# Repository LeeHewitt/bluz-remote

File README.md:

Bluz Remote Files
==========
Bluz is a Development Kit (DK) that implements the Wiring language and talks to the [Particle](https://www.particle.io/) cloud through Bluetooth Low Energy. It can be accessed through a REST API and programmed from a Web IDE.

The Bluz Remote is a device that can be used to control many Particle projects. It provides a simple layout for buttons thaqt publish events, the events can then be subscribed to by various Particle services for control.

Example projects to control include:
* Robotic projects 
* IR Transmitters to control TV's, DVD's, etc
* RF Transmitters to control light switches, outlets, etc

Project Page: https://www.hackster.io/eely22/universe-remote-5830e2

###PCB 
The PCB is available on OSH Park:

<a href="https://oshpark.com/shared_projects/SAVrwlZ8"></img></a> 

##Sections
<b>BOM</b>: Current Bill of Materials for the remote.

<b>HW Design</b>: Schematics, board layouts, and other design files.

<b>3D Files</b>: 3D Models of the PCBA and Case

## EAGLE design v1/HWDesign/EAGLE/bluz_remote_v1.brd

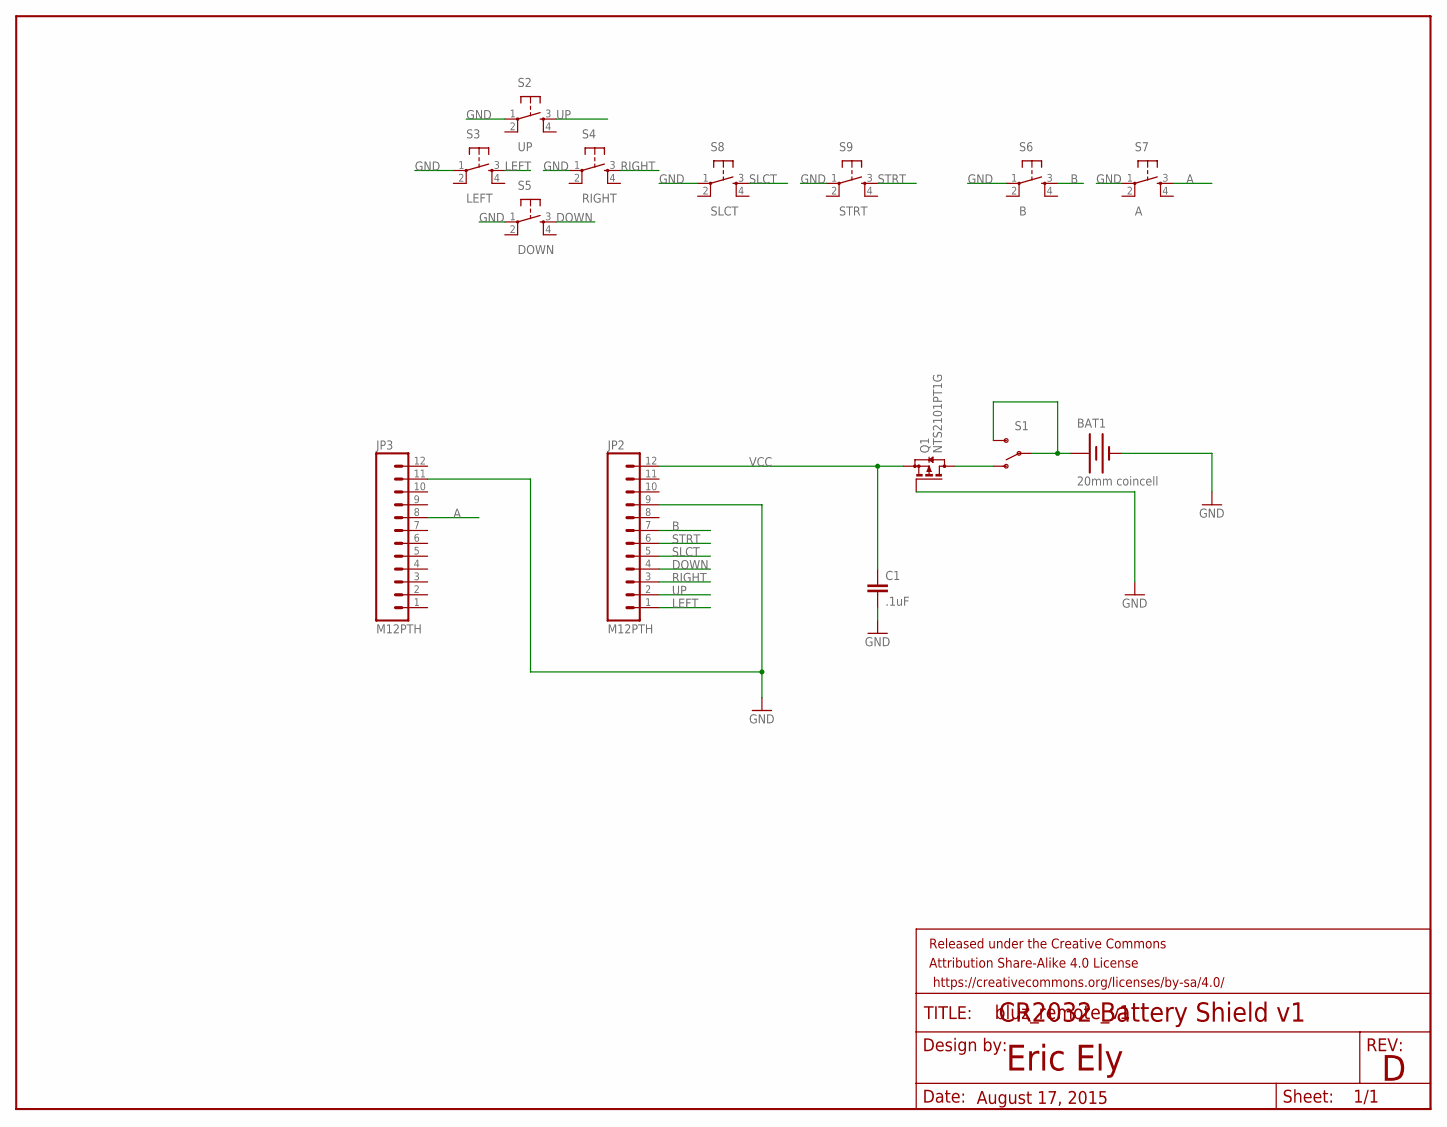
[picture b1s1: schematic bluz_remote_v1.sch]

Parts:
BAT1: 20mm coincell; BATTCON_20MM_4LEGS
C1: .1uF; 0603-CAP
FRAME1: FRAME-LETTER; CREATIVE_COMMONS
JP2, JP3: M12PTH; 1X12
Q1: NTS2101PT1G; SOT323
S1: SWITCH-SPDTKIT; SWITCH-SPDT_KIT
S2: UP; TACTILE_SWITCH_SMD
S3: LEFT; TACTILE_SWITCH_SMD
S4: RIGHT; TACTILE_SWITCH_SMD
S5: DOWN; TACTILE_SWITCH_SMD
S6: B; TACTILE_SWITCH_SMD
S7: A; TACTILE_SWITCH_SMD
S8: SLCT; TACTILE_SWITCH_SMD
S9: STRT; TACTILE_SWITCH_SMD

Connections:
A: JP3.8, S7.3
B: JP2.7, S6.3
DOWN: JP2.4, S5.3
GND: BAT1.2 (-), C1.2, JP2.9, JP3.11, Q1.1 (G), S2.1, S3.1, S4.1, S5.1, S6.1, S7.1, S8.1, S9.1
LEFT: JP2.1, S3.3
unnamed: BAT1.1 (+), S1.2, S1.3 (S)
unnamed: Q1.3 (D), S1.1 (O)
RIGHT: JP2.3, S4.3
SLCT: JP2.5, S8.3
STRT: JP2.6, S9.3
UP: JP2.2, S2.3
VCC: C1.1, JP2.12, Q1.2 (S)

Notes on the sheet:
Eric Ely
August 17, 2015
CR2032 Battery Shield v1

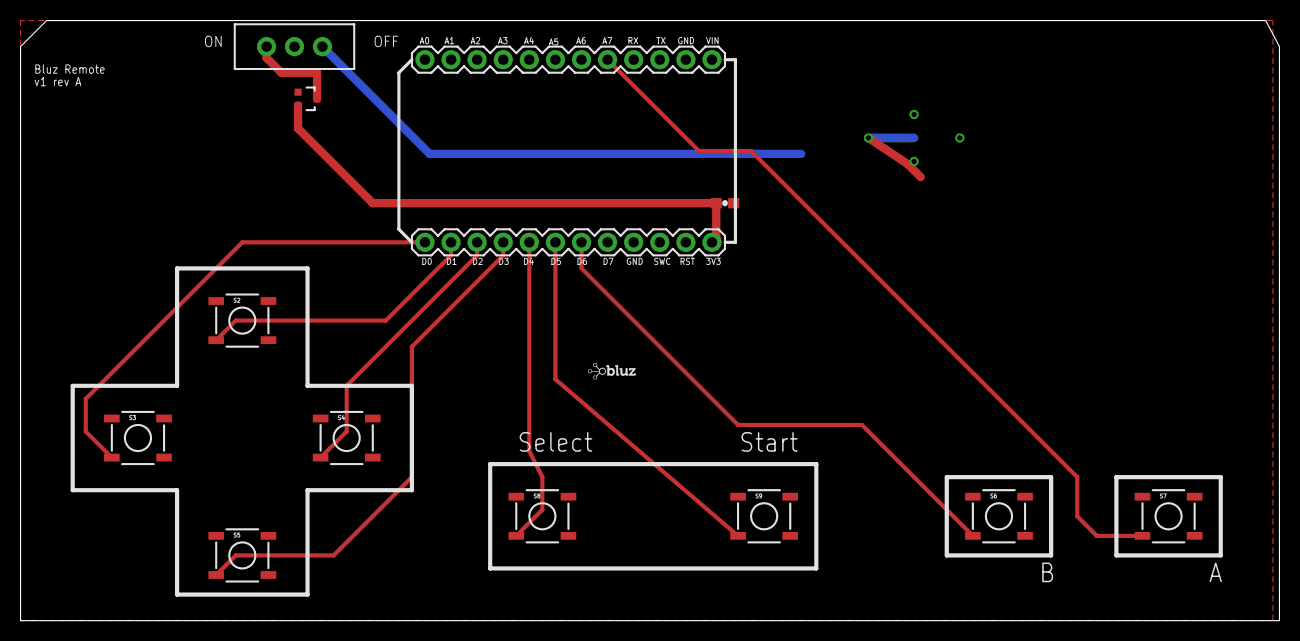
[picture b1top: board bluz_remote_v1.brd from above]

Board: 2 copper layers, 122.6 x 58.4 mm, 16 parts (1 on the bottom side), 12 nets.

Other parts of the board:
U$1: BLUZE_LOGO_LOW_RES

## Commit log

2017-02-18 Add OSH Park Buy Link
2017-02-18 Add Hackster page

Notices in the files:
parts and their libraries:
SparkFun-Electromechanical: Licensing: Creative Commons ShareAlike 4.0 International - https://creativecommons.org/licenses/by-sa/4.0
SparkFun-Aesthetics: Released under the Creative Commons Attribution Share-Alike 4.0 License
SparkFun-Aesthetics: https://creativecommons.org/licenses/by-sa/4.0
